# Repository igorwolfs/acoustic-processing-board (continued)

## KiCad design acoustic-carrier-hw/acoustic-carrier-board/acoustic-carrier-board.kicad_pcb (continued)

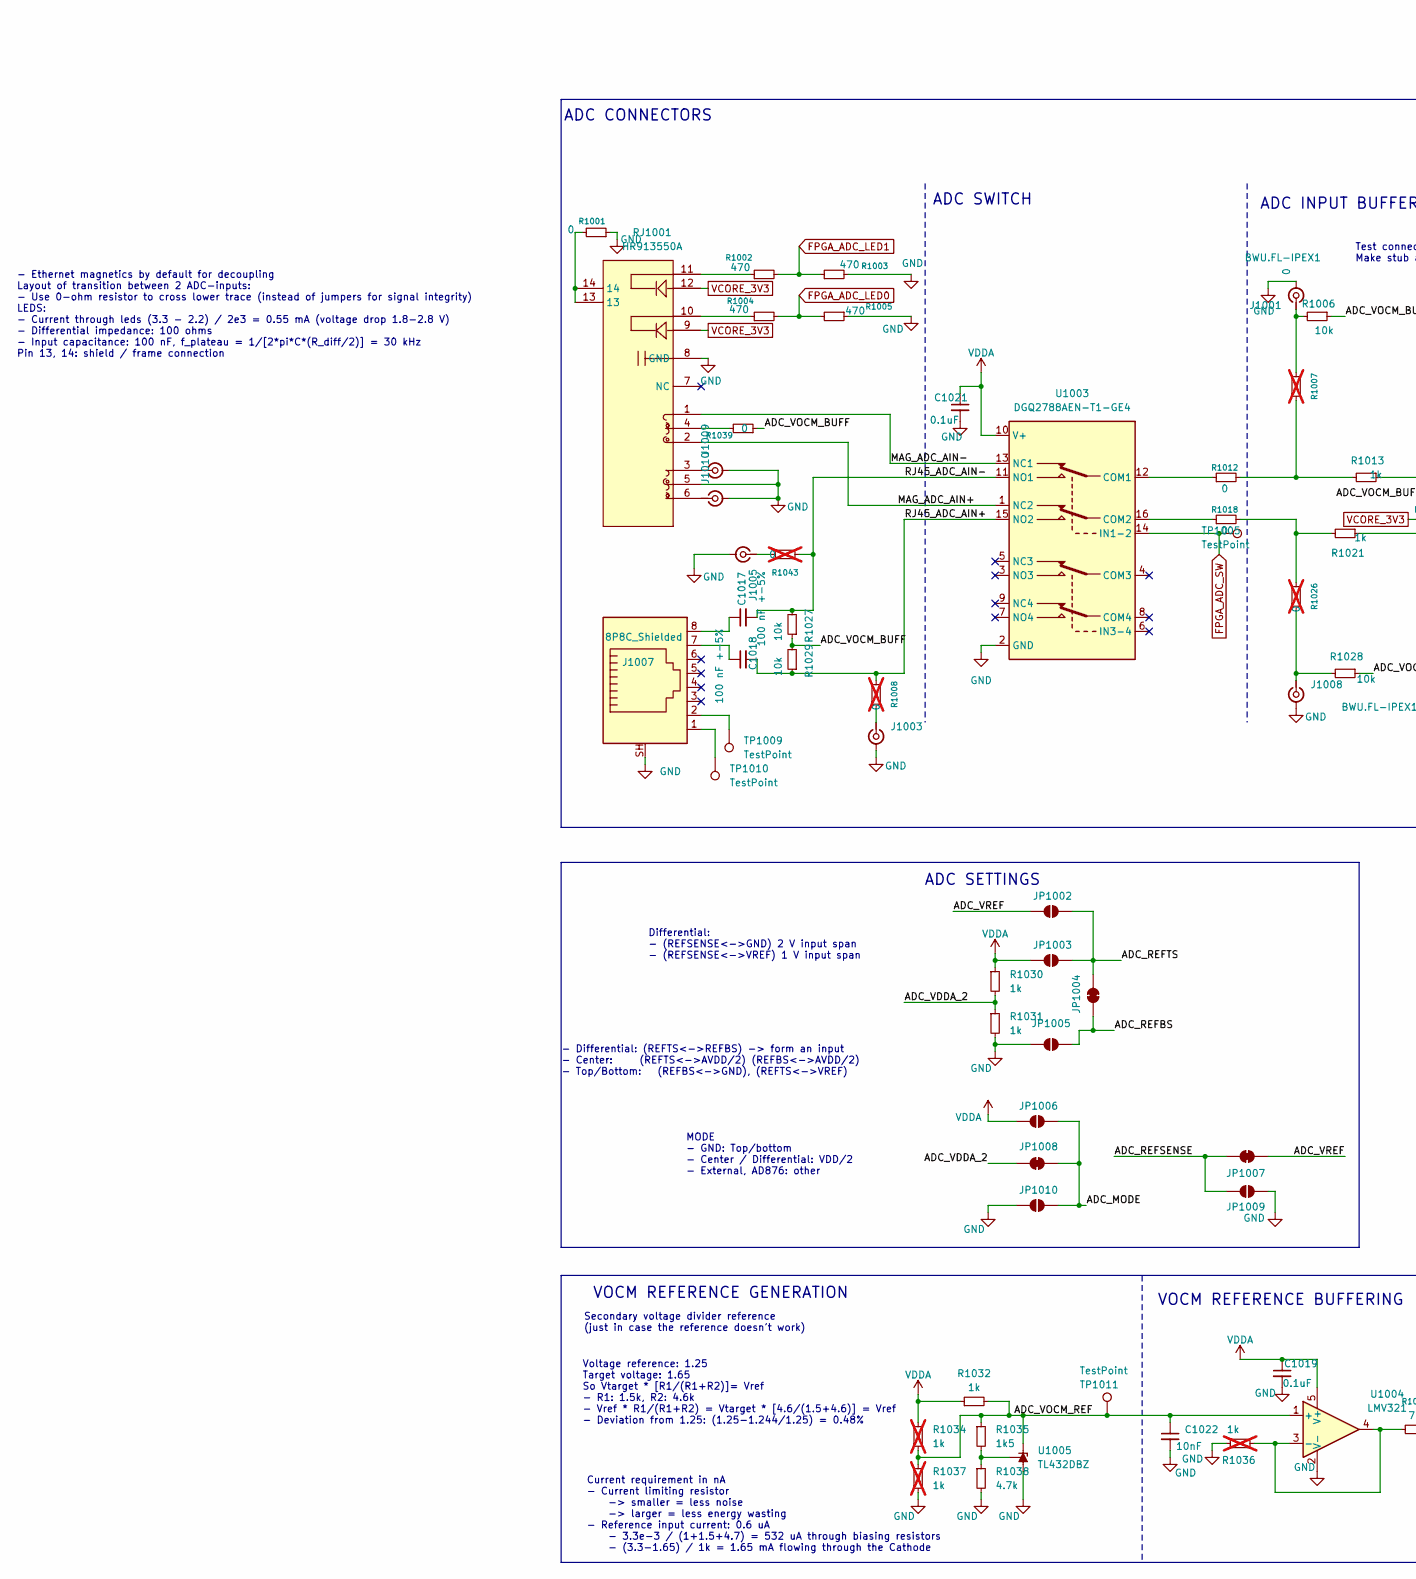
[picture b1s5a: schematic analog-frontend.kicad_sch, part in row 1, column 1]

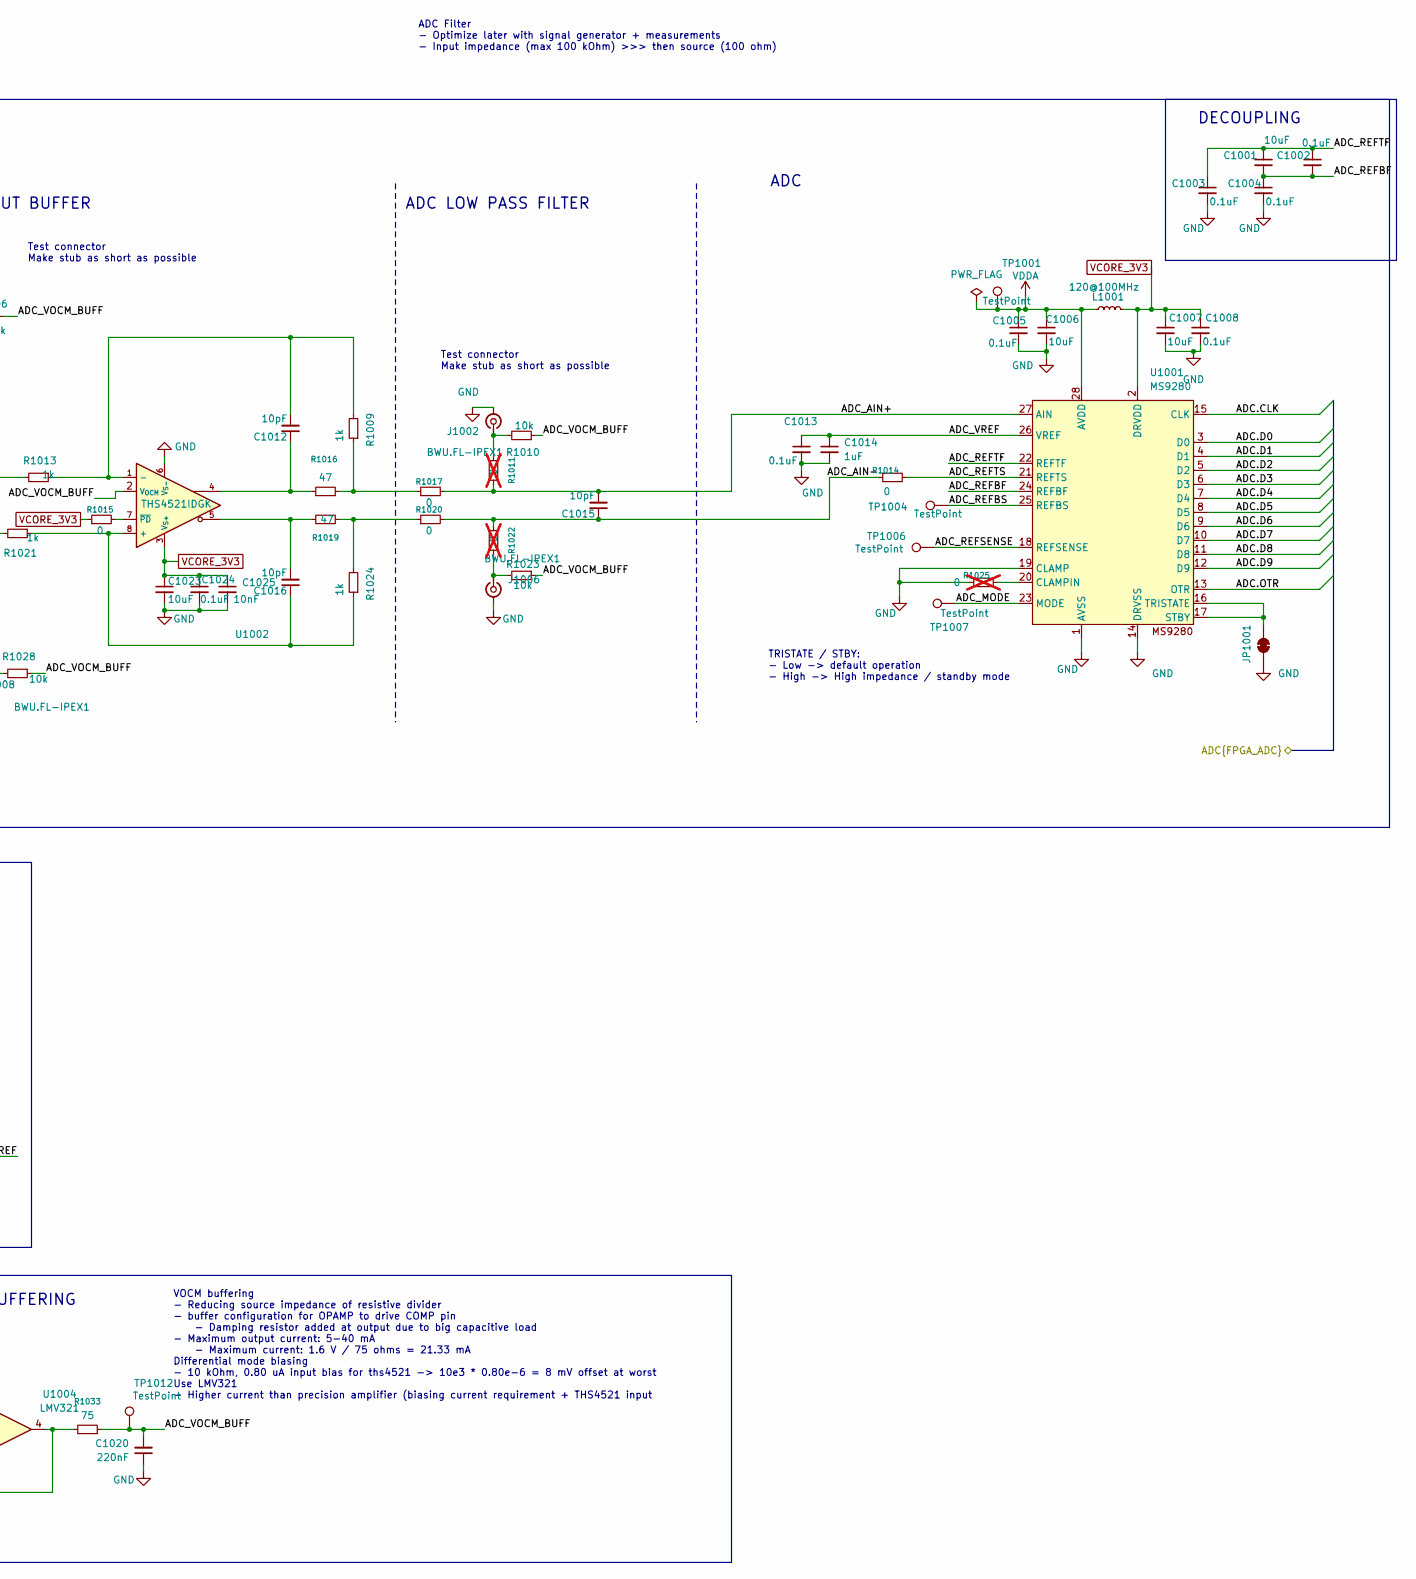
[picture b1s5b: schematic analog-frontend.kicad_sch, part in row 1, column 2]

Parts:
C1001, C1006, C1007, C1023: 10uF; C_0603_1608Metric; MPN CL10A106KP8NNNC
C1002, C1003, C1004, C1005, C1008, C1013, C1019, C1021, C1024: 0.1uF; C_0201_0603Metric; MPN CGA0201X7R104K160ET
C1012, C1015, C1016: 10pF; C_0603_1608Metric_Pad1.08x0.95mm_HandSolder; MPN CL10C100JB8NNNC
C1014: 1uF; C_0805_2012Metric; MPN CL21B105KBFNNNE
C1017, C1018: 100 nF +-5%; C_0603_1608Metric_Pad1.08x0.95mm_HandSolder; MPN 0603B104J500NT
C1020: 220nF; C_0402_1005Metric; MPN CL05B224KO5NNNC
C1022, C1025: 10nF; C_0201_0603Metric; MPN 0201B103K250NT
J1001, J1002, J1003, J1005, J1006, J1008, J1009, J1010: BWU.FL-IPEX1; MPN BWU.FL-IPEX1
J1007: 8P8C_Shielded; RJ45_RCH_RC01937; MPN RC01937
JP1001, JP1004, JP1007, JP1008: SolderJumper_2_Bridged; SolderJumper-2_P1.3mm_Bridged_Pad1.0x1.5mm
JP1002, JP1003, JP1005, JP1006, JP1009, JP1010: SolderJumper_2_Open; SolderJumper-2_P1.3mm_Open_Pad1.0x1.5mm
L1001: 120@100MHz; L_0603_1608Metric; MPN BLM18SG121TN1D
R1001: 0; R_0603_1608Metric_Pad0.98x0.95mm_HandSolder; MPN 0603WAF0000T5E
R1002, R1003, R1004, R1005: 470; R_0603_1608Metric; MPN 0603WAF4700T5E
R1006, R1010, R1023, R1027, R1028, R1029: 10k; R_0603_1608Metric; MPN 0603WAF1002T5E
R1007, R1008, R1011, R1022, R1025, R1026, R1043: 0; R_0603_1608Metric; MPN 0603WAF0000T5E; not fitted
R1009, R1013, R1021, R1024, R1030, R1031, R1032: 1k; R_0603_1608Metric; MPN 0603WAF1001T5E
R1012, R1015, R1017, R1018, R1020: 0; R_0402_1005Metric_Pad0.72x0.64mm_HandSolder; MPN 0402WGF0000TCE
R1014, R1039: 0; R_0603_1608Metric; MPN 0603WAF0000T5E
R1016, R1019: 47; R_0603_1608Metric; MPN 0603WAF470JT5E
R1033: 75; R_0603_1608Metric; MPN 0603WAF750JT5E
R1034, R1036, R1037: 1k; R_0603_1608Metric; MPN C21190; not fitted
R1035: 1k5; R_0603_1608Metric; MPN 0603WAF1501T5E
R1038: 4.7k; R_0603_1608Metric; MPN 0603WAF4701T5E
RJ1001: HR913550A; RJ45-TH_HR913550A; MPN HR913550A
TP1001, TP1004, TP1006, TP1007, TP1009, TP1010, TP1011, TP1012: TestPoint; TestPoint_Loop_D1.80mm_Drill1.0mm_Beaded
TP1005: TestPoint; TestPoint_THTPad_1.5x1.5mm_Drill0.7mm
U1001: MS9280; SSOP-28_5.3x10.2mm_P0.65mm; MPN MS9280
U1002: THS4521IDGK; VSSOP-8_3x3mm_P0.65mm; MPN THS4521IDGKR
U1003: DGQ2788AEN-T1-GE4; QFN40P260X180X60-16N_Fv1.2; MPN DGQ2788AEN-T1-GE4
U1004: LMV321; SOT-23-5; MPN LMV321IDBVR
U1005: TL432DBZ; SOT-23; MPN TL432

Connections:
/ADC.CLK: U1001.15 (CLK); also elsewhere on the board
/ADC.D0: U1001.3 (D0); also elsewhere on the board
/ADC.D1: U1001.4 (D1); also elsewhere on the board
/ADC.D2: U1001.5 (D2); also elsewhere on the board
/ADC.D3: U1001.6 (D3); also elsewhere on the board
/ADC.D4: U1001.7 (D4); also elsewhere on the board
/ADC.D5: U1001.8 (D5); also elsewhere on the board
/ADC.D6: U1001.9 (D6); also elsewhere on the board
/ADC.D7: U1001.10 (D7); also elsewhere on the board
/ADC.D8: U1001.11 (D8); also elsewhere on the board
/ADC.D9: U1001.12 (D9); also elsewhere on the board
/ADC.OTR: U1001.13 (OTR); also elsewhere on the board
/ANALOG-FRONTEND/ADC_AIN+: C1015.2, R1011.1, R1017.2, U1001.27 (AIN)
/ANALOG-FRONTEND/ADC_AIN-: C1015.1, R1014.1, R1020.2, R1022.1
/ANALOG-FRONTEND/ADC_MODE: JP1006.2 (B), JP1008.2 (B), JP1010.2 (B), TP1007.1, U1001.23 (MODE)
/ANALOG-FRONTEND/ADC_REFBF: C1001.2, C1002.2, C1004.1, U1001.24 (REFBF)
/ANALOG-FRONTEND/ADC_REFBS: JP1004.1 (A), JP1005.2 (B), TP1004.1, U1001.25 (REFBS)
/ANALOG-FRONTEND/ADC_REFSENSE: JP1007.2 (B), JP1009.2 (B), TP1006.1, U1001.18 (REFSENSE)
/ANALOG-FRONTEND/ADC_REFTF: C1001.1, C1002.1, C1003.1, U1001.22 (REFTF)
/ANALOG-FRONTEND/ADC_REFTS: JP1002.2 (B), JP1003.2 (B), JP1004.2 (B), R1014.2, U1001.21 (REFTS)
/ANALOG-FRONTEND/ADC_VDDA_2: JP1008.1 (A), R1030.2, R1031.1
/ANALOG-FRONTEND/ADC_VOCM_BUFF: C1020.2, R1006.1, R1010.1, R1023.1, R1027.1, R1028.1, R1029.2, R1033.1, R1039.1, TP1012.1, U1002.2 (V_{OCM})
/ANALOG-FRONTEND/ADC_VOCM_REF: C1022.1, R1032.2, R1034.2, R1035.1, R1037.1, TP1011.1, U1004.1 (+), U1005.2 (K)
/ANALOG-FRONTEND/ADC_VREF: C1013.1, C1014.1, JP1002.1 (A), JP1007.1 (A), U1001.26 (VREF)
/ANALOG-FRONTEND/MAG_ADC_AIN+: RJ1001.2, U1003.1 (NC2)
/ANALOG-FRONTEND/MAG_ADC_AIN-: RJ1001.1, U1003.13 (NC1)
/ANALOG-FRONTEND/RJ45_ADC_AIN+: C1018.2, R1008.1, R1029.1, U1003.15 (NO2)
/ANALOG-FRONTEND/RJ45_ADC_AIN-: C1017.2, R1027.2, R1043.1, U1003.11 (NO1)
FPGA_ADC_LED0: R1004.2, R1005.2; also elsewhere on the board
FPGA_ADC_LED1: R1002.2, R1003.1; also elsewhere on the board
FPGA_ADC_SW: TP1005.1, U1003.14 (IN1-2); also elsewhere on the board
GND: C1003.2, C1004.2, C1005.2, C1006.2, C1007.2, C1008.2, C1013.2, C1014.2, C1019.2, C1020.1, C1021.2, C1022.2, C1023.2, C1024.2, C1025.2, J1001.2 (Ext), J1002.2 (Ext), J1003.2 (Ext), J1005.2 (Ext), J1006.2 (Ext), J1007.SH, J1008.2 (Ext), J1009.2 (Ext), J1010.2 (Ext), JP1001.1 (A), JP1005.1 (A), JP1009.1 (A), JP1010.1 (A), R1001.1, R1003.2, R1005.1, R1025.1, R1031.2, R1036.1, R1037.2, R1038.2, RJ1001.5, RJ1001.8 (GND), U1001.1 (AVSS), U1001.14 (DRVSS), U1001.19 (CLAMP), U1002.6 (V_{S-}), U1003.2 (GND), U1004.2 (V-), U1005.3 (A); also elsewhere on the board
unnamed: C1012.1, R1016.2, U1002.4
unnamed: C1016.2, R1019.2, U1002.5
unnamed: C1017.1, J1007.8
unnamed: C1018.1, J1007.7
unnamed: J1001.1 (In), R1006.2, R1007.1
unnamed: J1002.1 (In), R1010.2, R1011.2
unnamed: J1003.1 (In), R1008.2
unnamed: J1005.1 (In), R1043.2
unnamed: J1006.1 (In), R1022.2, R1023.2
unnamed: J1007.1, TP1010.1
unnamed: J1007.2, TP1009.1
unnamed: J1008.1 (In), R1026.2, R1028.2
unnamed: J1009.1 (In), RJ1001.3
unnamed: J1010.1 (In), RJ1001.6
unnamed: JP1001.2 (B), U1001.16 (TRISTATE), U1001.17 (STBY)
unnamed: R1001.2, RJ1001.13, RJ1001.14
unnamed: R1002.1, RJ1001.11
unnamed: R1004.1, RJ1001.10
unnamed: R1007.2, R1012.2, R1013.2
unnamed: R1009.1, R1016.1, R1017.1
unnamed: R1018.2, R1021.2, R1026.1
unnamed: R1019.1, R1020.1, R1024.2
unnamed: R1039.2, RJ1001.4
unnamed: R1025.2, U1001.20 (CLAMPIN)
unnamed: C1016.1, R1021.1, R1024.1, U1002.8 (+)
unnamed: C1012.2, R1009.2, R1013.1, U1002.1 (-)
unnamed: R1015.2, U1002.7 (~PD)
unnamed: R1012.1, U1003.12 (COM1)
unnamed: R1018.1, U1003.16 (COM2)
unnamed: R1033.2, R1036.2, U1004.3 (-), U1004.4
unnamed: R1035.2, R1038.1, U1005.1 (REF)
VCORE_3V3: C1007.1, C1008.1, C1023.1, C1024.1, C1025.1, L1001.1, R1015.1, RJ1001.9, RJ1001.12, U1001.2 (DRVDD), U1002.3 (V_{S+}); also elsewhere on the board
VDDA: C1005.1, C1006.1, C1019.1, C1021.1, JP1003.1 (A), JP1006.1 (A), L1001.2, R1030.1, R1032.1, R1034.1, TP1001.1, U1001.28 (AVDD), U1003.10 (V+), U1004.5 (V+)

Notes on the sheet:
ADC INPUT BUFFER
ADC
Secondary voltage divider reference (just in case the reference doesn't work)
VOCM REFERENCE GENERATION
Differential: - (REFSENSE<->GND) 2 V input span - (REFSENSE<->VREF) 1 V input span
ADC LOW PASS FILTER
MODE - GND: Top/bottom - Center / Differential: VDD/2 - External, AD876: other
VOCM buffering - Reducing source impedance of resistive divider - buffer configuration for OPAMP to drive COMP pin - Damping resistor added at output due to big capacitive load - Maximum output current: 5-40 mA - Maximum current: 1.6 V / 75 ohms = 21.33 mA Differential mode biasing - 10 kOhm, 0.80 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
ADC CONNECTORS
Test connector Make stub as short as possible
ADC SWITCH
Voltage reference: 1.25 Target voltage: 1.65 So Vtarget * [R1/(R1+R2)]= Vref - R1: 1.5k, R2: 4.6k - Vref * R1/(R1+R2) = Vtarget * [4.6/(1.5+4.6)] = Vref - Deviation from 1.25: (1.25-1.244/1.25) = 0.48%
ADC Filter - Optimize later with signal generator + measurements - Input impedance (max 100 kOhm) >>> then source (100 ohm)
TRISTATE / STBY: - Low -> default operation - High -> High impedance / standby mode
VOCM REFERENCE BUFFERING
- Ethernet magnetics by default for decoupling Layout of transition between 2 ADC-inputs: - Use 0-ohm resistor to cross lower trace (instead of jumpers for signal integrity) LEDS: - Current through leds (3.3 - 2.2) / 2e3 = 0.55 mA (voltage drop 1.8-2.8 V) - Differential impedance: 100 ohms - Input 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
DECOUPLING
ADC SETTINGS
Current requirement in nA - Current limiting resistor -> smaller = less noise -> larger = less energy wasting - Reference input current: 0.6 uA - 3.3e-3 / (1+1.5+4.7) = 532 uA through biasing resistors - (3.3-1.65) / 1k = 1.65 mA flowing through the Cathode
- Differential: (REFTS<->REFBS) -> form an input - Center: (REFTS<->AVDD/2) (REFBS<->AVDD/2) - Top/Bottom: (REFBS<->GND), (REFTS<->VREF)

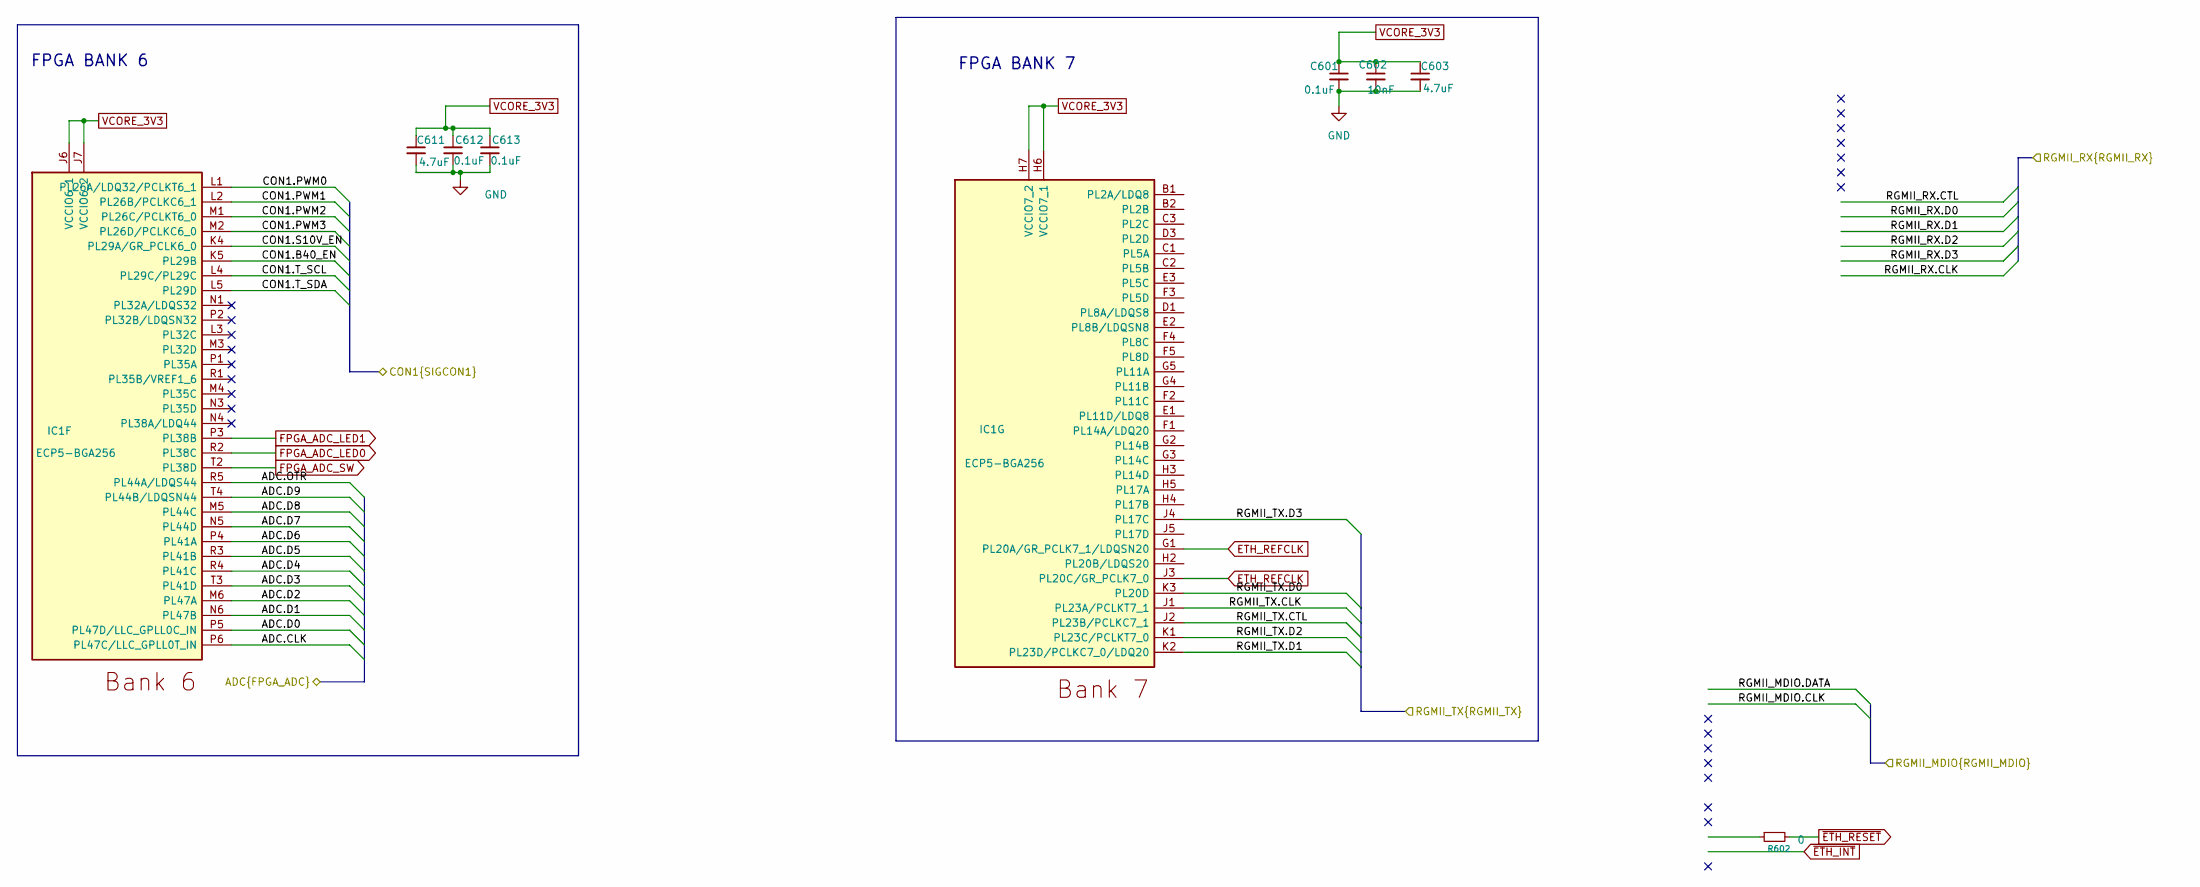
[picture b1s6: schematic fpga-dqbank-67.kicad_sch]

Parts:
C601, C612, C613: 0.1uF; C_0201_0603Metric; MPN CGA0201X7R104K160ET
C602: 10nF; C_0201_0603Metric; MPN 0201B103K250NT
C603, C611: 4.7uF; C_0402_1005Metric; MPN CL05A475MP5NRNC
IC1: ECP5-BGA256; BGA256C80P16X16_1400X1400X170; MPN LFE5U-25F-6BG256C
R602: 0; R_0603_1608Metric; MPN 0603WAF0000T5E

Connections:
/ADC.CLK: IC1.P6 (PL47C/LLC_GPLL0T_IN); also elsewhere on the board
/ADC.D0: IC1.P5 (PL47D/LLC_GPLL0C_IN); also elsewhere on the board
/ADC.D1: IC1.N6 (PL47B); also elsewhere on the board
/ADC.D2: IC1.M6 (PL47A); also elsewhere on the board
/ADC.D3: IC1.T3 (PL41D); also elsewhere on the board
/ADC.D4: IC1.R4 (PL41C); also elsewhere on the board
/ADC.D5: IC1.R3 (PL41B); also elsewhere on the board
/ADC.D6: IC1.P4 (PL41A); also elsewhere on the board
/ADC.D7: IC1.N5 (PL44D); also elsewhere on the board
/ADC.D8: IC1.M5 (PL44C); also elsewhere on the board
/ADC.D9: IC1.T4 (PL44B/LDQSN44); also elsewhere on the board
/ADC.OTR: IC1.R5 (PL44A/LDQS44); also elsewhere on the board
/CON1.B40_EN: IC1.K5 (PL29B); also elsewhere on the board
/CON1.PWM0: IC1.L1 (PL26A/LDQ32/PCLKT6_1); also elsewhere on the board
/CON1.PWM1: IC1.L2 (PL26B/PCLKC6_1); also elsewhere on the board
/CON1.PWM2: IC1.M1 (PL26C/PCLKT6_0); also elsewhere on the board
/CON1.PWM3: IC1.M2 (PL26D/PCLKC6_0); also elsewhere on the board
/CON1.S10V_EN: IC1.K4 (PL29A/GR_PCLK6_0); also elsewhere on the board
/CON1.T_SCL: IC1.L4 (PL29C/PL29C); also elsewhere on the board
/CON1.T_SDA: IC1.L5 (PL29D); also elsewhere on the board
/RGMII_TX.CLK: IC1.J1 (PL23A/PCLKT7_1); also elsewhere on the board
/RGMII_TX.CTL: IC1.J2 (PL23B/PCLKC7_1); also elsewhere on the board
/RGMII_TX.D0: IC1.K3 (PL20D); also elsewhere on the board
/RGMII_TX.D1: IC1.K2 (PL23D/PCLKC7_0/LDQ20); also elsewhere on the board
/RGMII_TX.D2: IC1.K1 (PL23C/PCLKT7_0); also elsewhere on the board
/RGMII_TX.D3: IC1.J4 (PL17C); also elsewhere on the board
ETH_REFCLK: IC1.G1 (PL20A/GR_PCLK7_1/LDQSN20), IC1.J3 (PL20C/GR_PCLK7_0); also elsewhere on the board
FPGA_ADC_LED0: IC1.R2 (PL38C); also elsewhere on the board
FPGA_ADC_LED1: IC1.P3 (PL38B); also elsewhere on the board
FPGA_ADC_SW: IC1.T2 (PL38D); also elsewhere on the board
GND: C601.2, C602.2, C603.2, C611.2, C612.2, C613.2; also elsewhere on the board
VCORE_3V3: C601.1, C602.1, C603.1, C611.1, C612.1, C613.1, IC1.H6 (VCCIO7_1), IC1.H7 (VCCIO7_2), IC1.J6 (VCCIO6_1), IC1.J7 (VCCIO6_2); also elsewhere on the board
~ETH_RESET: R602.2; also elsewhere on the board

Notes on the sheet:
FPGA BANK 6
FPGA BANK 7

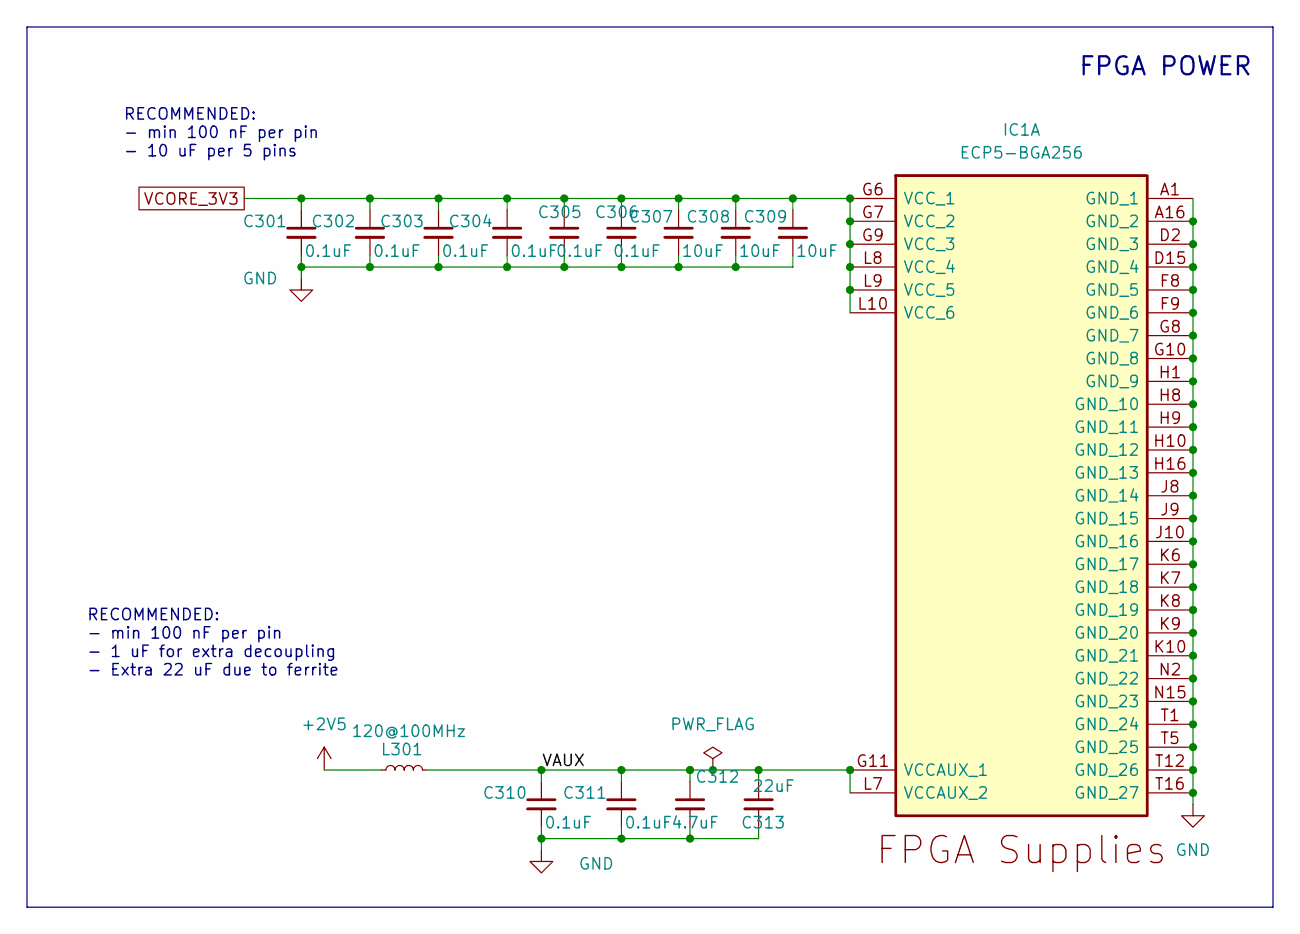
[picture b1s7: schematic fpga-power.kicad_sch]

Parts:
C301, C302, C303, C304, C305, C306, C310, C311: 0.1uF; C_0201_0603Metric; MPN CGA0201X7R104K160ET
C307, C308, C309: 10uF; C_0603_1608Metric; MPN CL10A106KP8NNNC
C312: 4.7uF; C_0402_1005Metric; MPN CL05A475MP5NRNC
C313: 22uF; C_0603_1608Metric; MPN CL10A226MQ8NRNC
IC1: ECP5-BGA256; BGA256C80P16X16_1400X1400X170; MPN LFE5U-25F-6BG256C
L301: 120@100MHz; L_0603_1608Metric; MPN BLM18SG121TN1D

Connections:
+2V5: L301.2; also elsewhere on the board
/FPGA-POWER/VAUX: C310.1, C311.1, C312.1, C313.1, IC1.G11 (VCCAUX_1), IC1.L7 (VCCAUX_2), L301.1
GND: C301.2, C302.2, C303.2, C304.2, C305.2, C306.2, C307.2, C308.2, C309.2, C310.2, C311.2, C312.2, C313.2, IC1.A1 (GND_1), IC1.A16 (GND_2), IC1.D2 (GND_3), IC1.D15 (GND_4), IC1.F8 (GND_5), IC1.F9 (GND_6), IC1.G8 (GND_7), IC1.G10 (GND_8), IC1.H1 (GND_9), IC1.H8 (GND_10), IC1.H9 (GND_11), IC1.H10 (GND_12), IC1.H16 (GND_13), IC1.J8 (GND_14), IC1.J9 (GND_15), IC1.J10 (GND_16), IC1.K6 (GND_17), IC1.K7 (GND_18), IC1.K8 (GND_19), IC1.K9 (GND_20), IC1.K10 (GND_21), IC1.N2 (GND_22), IC1.N15 (GND_23), IC1.T1 (GND_24), IC1.T5 (GND_25), IC1.T12 (GND_26), IC1.T16 (GND_27); also elsewhere on the board
VCORE_3V3: C301.1, C302.1, C303.1, C304.1, C305.1, C306.1, C307.1, C308.1, C309.1, IC1.G6 (VCC_1), IC1.G7 (VCC_2), IC1.G9 (VCC_3), IC1.L8 (VCC_4), IC1.L9 (VCC_5), IC1.L10 (VCC_6); also elsewhere on the board

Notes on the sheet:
RECOMMENDED: - min 100 nF per pin - 10 uF per 5 pins
RECOMMENDED: - min 100 nF per pin - 1 uF for extra decoupling - Extra 22 uF due to ferrite
FPGA POWER

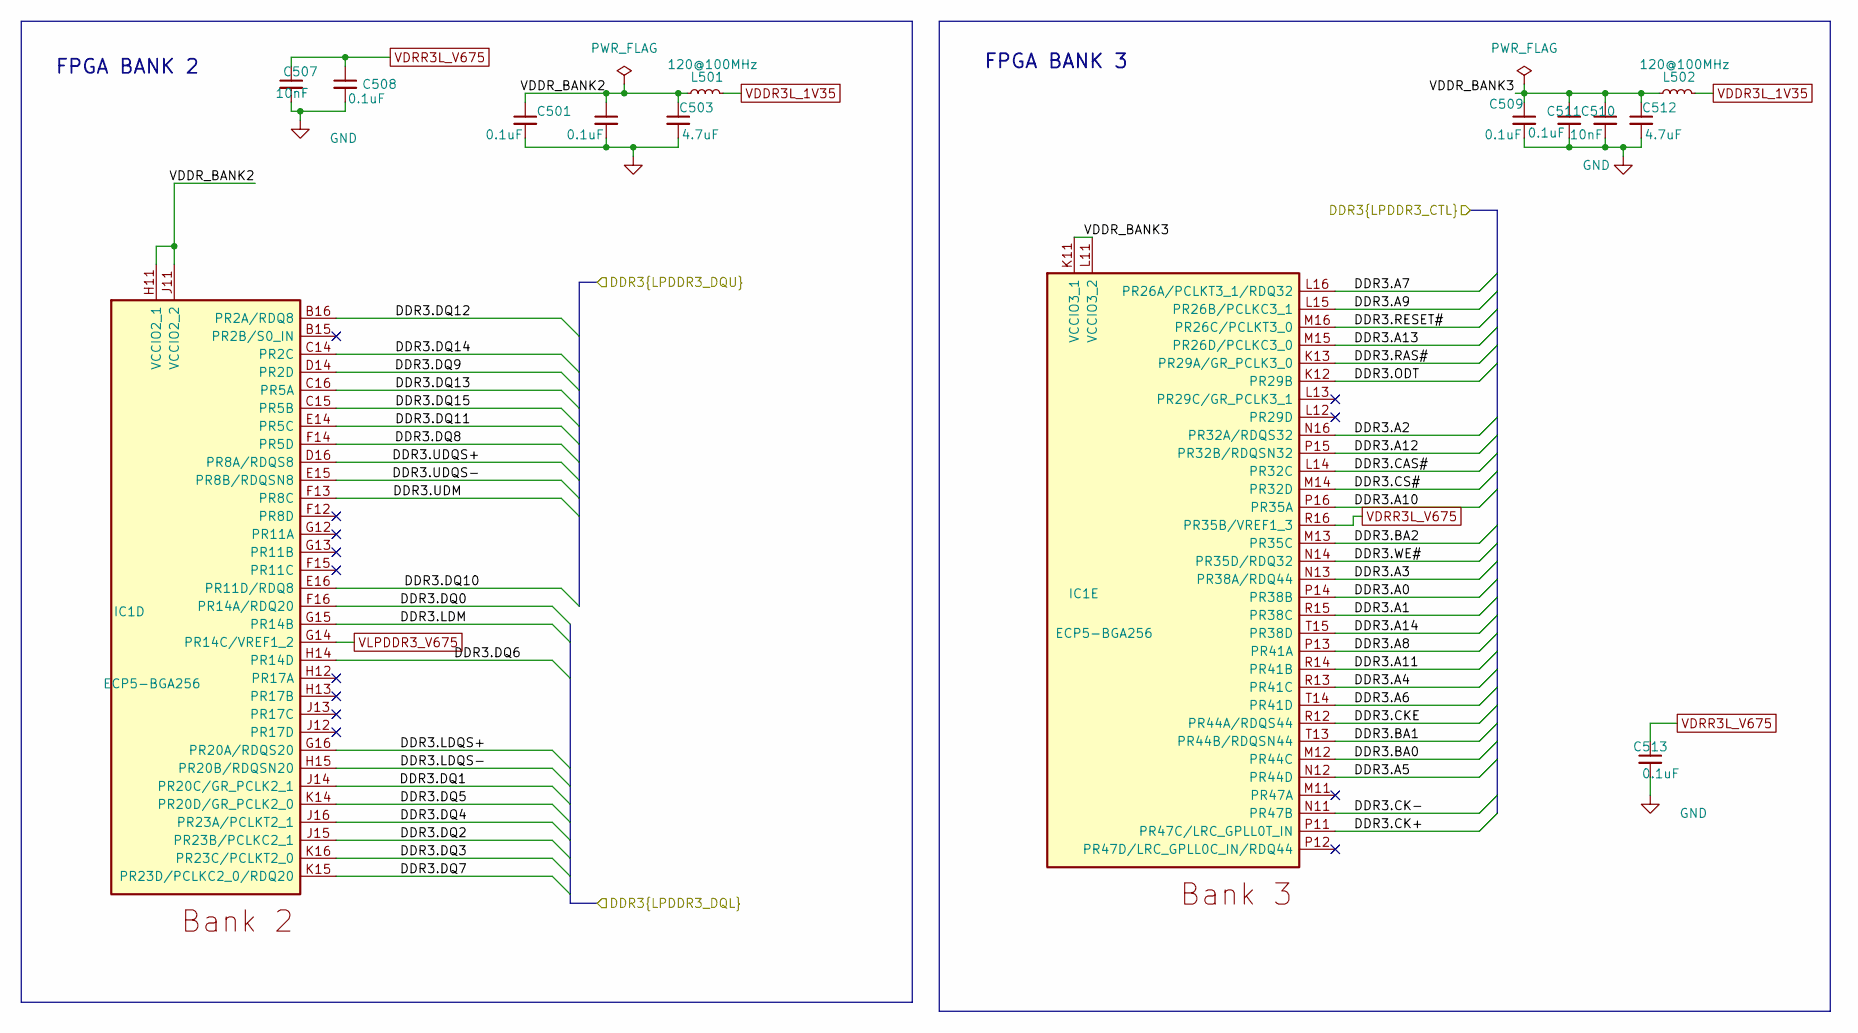
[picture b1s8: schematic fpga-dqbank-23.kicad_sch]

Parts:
C501, C502, C508, C509, C510, C513: 0.1uF; C_0201_0603Metric; MPN CGA0201X7R104K160ET
C503, C512: 4.7uF; C_0402_1005Metric; MPN CL05A475MP5NRNC
C507, C511: 10nF; C_0201_0603Metric; MPN 0201B103K250NT
IC1: ECP5-BGA256; BGA256C80P16X16_1400X1400X170; MPN LFE5U-25F-6BG256C
L501, L502: 120@100MHz; L_0603_1608Metric; MPN BLM18SG121TN1D

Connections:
/DDR3/DDR3.A0: IC1.P14 (PR38B); also elsewhere on the board
/DDR3/DDR3.A1: IC1.R15 (PR38C); also elsewhere on the board
/DDR3/DDR3.A2: IC1.N16 (PR32A/RDQS32); also elsewhere on the board
/DDR3/DDR3.A3: IC1.N13 (PR38A/RDQ44); also elsewhere on the board
/DDR3/DDR3.A4: IC1.R13 (PR41C); also elsewhere on the board
/DDR3/DDR3.A5: IC1.N12 (PR44D); also elsewhere on the board
/DDR3/DDR3.A6: IC1.T14 (PR41D); also elsewhere on the board
/DDR3/DDR3.A7: IC1.L16 (PR26A/PCLKT3_1/RDQ32); also elsewhere on the board
/DDR3/DDR3.A8: IC1.P13 (PR41A); also elsewhere on the board
/DDR3/DDR3.A9: IC1.L15 (PR26B/PCLKC3_1); also elsewhere on the board
/DDR3/DDR3.A10: IC1.P16 (PR35A); also elsewhere on the board
/DDR3/DDR3.A11: IC1.R14 (PR41B); also elsewhere on the board
/DDR3/DDR3.A12: IC1.P15 (PR32B/RDQSN32); also elsewhere on the board
/DDR3/DDR3.A13: IC1.M15 (PR26D/PCLKC3_0); also elsewhere on the board
/DDR3/DDR3.A14: IC1.T15 (PR38D); also elsewhere on the board
/DDR3/DDR3.BA0: IC1.M12 (PR44C); also elsewhere on the board
/DDR3/DDR3.BA1: IC1.T13 (PR44B/RDQSN44); also elsewhere on the board
/DDR3/DDR3.BA2: IC1.M13 (PR35C); also elsewhere on the board
/DDR3/DDR3.CAS#: IC1.L14 (PR32C); also elsewhere on the board
/DDR3/DDR3.CK+: IC1.P11 (PR47C/LRC_GPLL0T_IN); also elsewhere on the board
/DDR3/DDR3.CK-: IC1.N11 (PR47B); also elsewhere on the board
/DDR3/DDR3.CKE: IC1.R12 (PR44A/RDQS44); also elsewhere on the board
/DDR3/DDR3.CS#: IC1.M14 (PR32D); also elsewhere on the board
/DDR3/DDR3.DQ0: IC1.F16 (PR14A/RDQ20); also elsewhere on the board
/DDR3/DDR3.DQ1: IC1.J14 (PR20C/GR_PCLK2_1); also elsewhere on the board
/DDR3/DDR3.DQ2: IC1.J15 (PR23B/PCLKC2_1); also elsewhere on the board
/DDR3/DDR3.DQ3: IC1.K16 (PR23C/PCLKT2_0); also elsewhere on the board
/DDR3/DDR3.DQ4: IC1.J16 (PR23A/PCLKT2_1); also elsewhere on the board
/DDR3/DDR3.DQ5: IC1.K14 (PR20D/GR_PCLK2_0); also elsewhere on the board
/DDR3/DDR3.DQ6: IC1.H14 (PR14D); also elsewhere on the board
/DDR3/DDR3.DQ7: IC1.K15 (PR23D/PCLKC2_0/RDQ20); also elsewhere on the board
/DDR3/DDR3.DQ8: IC1.F14 (PR5D); also elsewhere on the board
/DDR3/DDR3.DQ9: IC1.D14 (PR2D); also elsewhere on the board
/DDR3/DDR3.DQ10: IC1.E16 (PR11D/RDQ8); also elsewhere on the board
/DDR3/DDR3.DQ11: IC1.E14 (PR5C); also elsewhere on the board
/DDR3/DDR3.DQ12: IC1.B16 (PR2A/RDQ8); also elsewhere on the board
/DDR3/DDR3.DQ13: IC1.C16 (PR5A); also elsewhere on the board
/DDR3/DDR3.DQ14: IC1.C14 (PR2C); also elsewhere on the board
/DDR3/DDR3.DQ15: IC1.C15 (PR5B); also elsewhere on the board
/DDR3/DDR3.LDM: IC1.G15 (PR14B); also elsewhere on the board
/DDR3/DDR3.LDQS+: IC1.G16 (PR20A/RDQS20); also elsewhere on the board
/DDR3/DDR3.LDQS-: IC1.H15 (PR20B/RDQSN20); also elsewhere on the board
/DDR3/DDR3.ODT: IC1.K12 (PR29B); also elsewhere on the board
/DDR3/DDR3.RAS#: IC1.K13 (PR29A/GR_PCLK3_0); also elsewhere on the board
/DDR3/DDR3.RESET#: IC1.M16 (PR26C/PCLKT3_0); also elsewhere on the board
/DDR3/DDR3.UDM: IC1.F13 (PR8C); also elsewhere on the board
/DDR3/DDR3.UDQS+: IC1.D16 (PR8A/RDQS8); also elsewhere on the board
/DDR3/DDR3.UDQS-: IC1.E15 (PR8B/RDQSN8); also elsewhere on the board
/DDR3/DDR3.WE#: IC1.N14 (PR35D/RDQ32); also elsewhere on the board
/FPGA-DQBANK-23/VDDR_BANK2: C501.1, C502.1, C503.1, IC1.H11 (VCCIO2_1), IC1.J11 (VCCIO2_2), L501.1
/FPGA-DQBANK-23/VDDR_BANK3: C509.1, C510.1, C511.1, C512.1, IC1.K11 (VCCIO3_1), IC1.L11 (VCCIO3_2), L502.1
GND: C501.2, C502.2, C503.2, C507.2, C508.2, C509.2, C510.2, C511.2, C512.2, C513.2; also elsewhere on the board
VDDR3L_1V35: L501.2, L502.2
VDRR3L_V675: C507.1, C508.1, C513.1, IC1.R16 (PR35B/VREF1_3)
VLPDDR3_V675: IC1.G14 (PR14C/VREF1_2); also elsewhere on the board

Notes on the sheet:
FPGA BANK 3
FPGA BANK 2

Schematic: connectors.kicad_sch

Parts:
J901: Conn_02x06_Odd_Even; PinSocket_2x06_P2.54mm_Horizontal; MPN PM254-2-06-W-8.5

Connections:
/CON1.B40_EN: J901.8; also elsewhere on the board
/CON1.PWM0: J901.1; also elsewhere on the board
/CON1.PWM1: J901.7; also elsewhere on the board
/CON1.PWM2: J901.11; also elsewhere on the board
/CON1.PWM3: J901.12; also elsewhere on the board
/CON1.S10V_EN: J901.10; also elsewhere on the board
/CON1.T_SCL: J901.6; also elsewhere on the board
/CON1.T_SDA: J901.4; also elsewhere on the board
GND: J901.3, J901.9; also elsewhere on the board

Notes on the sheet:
SIGNAL CONNECTOR

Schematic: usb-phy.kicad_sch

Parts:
C801, C807, C808, C809, C810, C811, C812, C816, C820, C821, C822: 0.1uF; C_0201_0603Metric; MPN CGA0201X7R104K160ET
C802, C817, C825: 10nF; C_0201_0603Metric; MPN 0201B103K250NT
C803, C806: 22pF; C_0402_1005Metric; MPN 0402CG220J500NT
C804, C805: 220pF; C_0402_1005Metric; MPN 0402B221K500NT
C813, C814, C819: 4.7uF; C_0402_1005Metric; MPN CL05A475MP5NRNC
D801, D802: LED_RED; LED_0603_1608Metric; MPN KT-0603R
J801: TYPE-C-31-M-12; USB_C_Receptacle_HRO_TYPE-C-31-M-12; MPN TYPE-C-31-M-12
R801: 220; R_0603_1608Metric; MPN 0603WAF2200T5E
R802, R812: 3k9; R_0603_1608Metric_Pad0.98x0.95mm_HandSolder; MPN 0603WAF3901T5E
R803, R811: 100k; R_0603_1608Metric_Pad0.98x0.95mm_HandSolder; MPN 0603WAF1003T5E
R804, R805: 5.1k; R_0603_1608Metric; Manufacturing part numb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 0805W8F5101T5E
R806: 1M; R_0402_1005Metric; MPN 0402WGF1004TCE
R807: 0; R_0402_1005Metric_Pad0.72x0.64mm_HandSolder; MPN 0402WGF0000TCE
R808: 12k+-1%; R_0603_1608Metric; MPN 0603WAF1202T5E
R809: 33k; R_0603_1608Metric; MPN 0603WAF3302T5E
R810: 33k; R_0603_1608Metric; Manufacturing part numb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 0603WAF3302T5E
R813, R821: 47; R_0603_1608Metric; MPN 0603WAF470JT5E
R814, R826: 4.7k; R_0603_1608Metric; MPN 0603WAF4701T5E
R815, R830: 1k; R_0603_1608Metric; MPN 0603WAF1001T5E
R816: 56k; R_0603_1608Metric_Pad0.98x0.95mm_HandSolder; MPN 0603WAF5602T5E
R818: 9k1; R_0603_1608Metric_Pad0.98x0.95mm_HandSolder; MPN 0603WAF9101T5E
TP801, TP804, TP807: TestPoint; TestPoint_Loop_D1.80mm_Drill1.0mm_Beaded
U801: USB3300-EZK; QFN32_5X5MC_MCH; MPN USB3300-EZK-TR
U802: LMV321; SOT-23-5; MPN LMV321IDBVR
U803, U804: SOT-23-5; MPN COS3201TR
Y801: Crystal_GND24_Small; Crystal_SMD_3225-4Pin_3.2x2.5mm; MPN X322524MSB4SI

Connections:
/POWER/USB_VBUS: C801.1, C807.1, C808.1, C822.1, J801.A4 (VBUS), J801.A9 (VBUS), J801.B4 (VBUS), J801.B9 (VBUS), R801.1, R809.1, R816.2, U802.5 (V+), U803.5 (V+), U804.5 (V+); also elsewhere on the board
/USB-PHY/USBCC_VREF_BUFF: R802.1, R812.1, TP801.1, U802.3 (-), U802.4
/USB-PHY/USB_CC1: C805.1, J801.A5 (CC1), R805.2, U804.4 (-)
/USB-PHY/USB_CC2: C804.1, J801.B5 (CC2), R804.2, U803.4 (-)
/USB-PHY/USB_D+: J801.A6 (DP1), J801.B6 (DP2), U801.7 (DP)
/USB-PHY/USB_D-: J801.A7 (DN1), J801.B7 (DN2), U801.8 (DM)
/USB-PHY/VDDA_USB1V8: C814.1, C816.1, U801.29 (VDDA1.8)
/USB-PHY/VDD_USB1V8: C819.1, C820.1, C821.1, U801.15 (VDD1.8), U801.26 (VDD1.8)
/USB.CLK: U801.14 (CLKOUT); also elsewhere on the board
/USB.D0: U801.24 (DATA0); also elsewhere on the board
/USB.D1: U801.23 (DATA1); also elsewhere on the board
/USB.D2: U801.22 (DATA2); also elsewhere on the board
/USB.D3: U801.21 (DATA3); also elsewhere on the board
/USB.D4: U801.20 (DATA4); also elsewhere on the board
/USB.D5: U801.19 (DATA5); also elsewhere on the board
/USB.D6: U801.18 (DATA6); also elsewhere on the board
/USB.D7: U801.17 (DATA7); also elsewhere on the board
/USB.DIR: U801.12 (DIR); also elsewhere on the board
/USB.NXT: U801.11 (NXT); also elsewhere on the board
/USB.RST: U801.9 (RESET); also elsewhere on the board
/USB.STP: U801.13 (STP); also elsewhere on the board
FPGA_CC1: R814.1; also elsewhere on the board
FPGA_CC2: R826.1; also elsewhere on the board
FPGA_USB_SENSE: R809.2, R810.1; also elsewhere on the board
GND: C801.2, C802.2, C803.1, C804.2, C805.2, C806.1, C807.2, C808.2, C809.2, C810.2, C811.2, C812.2, C813.2, C814.2, C816.2, C817.2, C819.2, C820.2, C821.2, C822.2, C825.2, J801.A1 (GND), J801.A12 (GND), J801.B1 (GND), J801.B12 (GND), J801.S1 (SHIELD), R804.1, R805.1, R808.1, R810.2, R815.2, R818.1, R830.2, U801.1 (GND), U801.2 (GND), U801.33 (EPAD), U802.2 (V-), U803.2 (V-), U804.2 (V-), Y801.2, Y801.4; also elsewhere on the board
unnamed: C806.2, R807.1, Y801.1
unnamed: D801.2 (A), R813.1, TP804.1
unnamed: D801.1 (K), R814.2, R815.1
unnamed: D802.2 (A), R821.1, TP807.1
unnamed: D802.1 (K), R826.2, R830.1
unnamed: R808.2, U801.32 (RBIAS)
unnamed: R801.2, U801.4 (VBUS)
unnamed: R806.1, R807.2, U801.28 (XI)
unnamed: C803.2, R806.2, U801.27 (XO), Y801.3
unnamed: C802.1, R816.1, R818.2, U802.1 (+)
unnamed: C817.1, R811.1, R812.2, U803.3 (+)
unnamed: R811.2, R813.2, U803.1 (OUT)
unnamed: C825.1, R802.2, R803.1, U804.3 (+)
unnamed: R803.2, R821.2, U804.1 (OUT)
VCORE_3V3: C809.1, C810.1, C811.1, C812.1, C813.1, U801.6 (VDD3.3), U801.16 (VDD3.3), U801.25 (VDD3.3), U801.30 (VDD3.3), U801.31 (REG_EN); also elsewhere on the board

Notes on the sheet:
Vbus sensing: 0.5/0.9 A @ 5V: Rsource = 51 kOhm, Vdiv = 0.45 V 1.5 A @ 5V: Rsource = 22 kOhm, Vdiv = 0.94 V 3 A @ 5V: Rsource = 10 kOhm, Vdiv = 1.69 V
VREF: - (9.1 / (9.1+56))*5 = 0.69 V
USB3300 ID PIN: - internally pulled HIGH (peripheral function, USB-B) DP - Termination included where necessary
USB_CC1: high -> USB_DIFF_SW: high -> D2 ACTIVE USB_CC2: high -> USB_DIFF_SW: low -> D1 ACTIVE
VREF: - 0.7 V = 5 * (9.1 / 9.1 + 56) SCHMITT TRIGGER BOUNDARIES: - (0.85 V, 0.67V), Vref: 0.7 V - Rs_CC <= 4 kOhm, Rs_Vref <= 5 ohms OUT: - Indicates sufficient power supply to FPGA - LED-ON if current sourcing > default LED - Vdrop: 2 V - I = (5-2)/1k = 3 mA V_FPGA: - 3.2-2.8 V
TODO: - Check here whether a pull-up is needed on D+ or whether the USB driver takes care of that - Check whether the hysteresis here actually connects to the right pair
Regulator enabled Decoupling detailed in datasheet
SWITCH - 51 ohm @ unused pins (avoid reflections) Switching voltage - 1.7-Vcc - Max Voltage: 7 V
USB PHY CONTROLLER
USB DECOUPLING
CC-SCHMITT TRIGGERS
